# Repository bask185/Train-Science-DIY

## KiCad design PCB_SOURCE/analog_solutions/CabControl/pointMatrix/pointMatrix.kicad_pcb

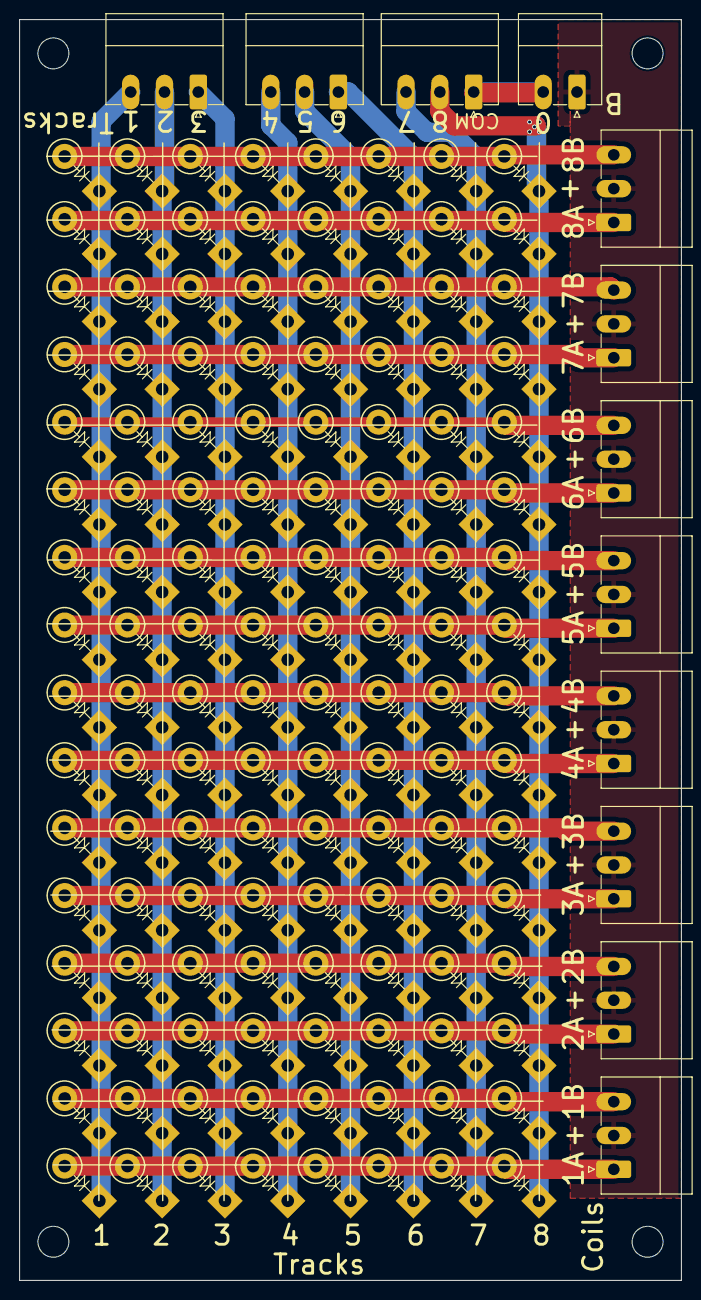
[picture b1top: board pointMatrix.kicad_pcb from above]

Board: 2 copper layers, 68.5 x 130.5 mm, 140 parts (0 on the bottom side), 26 nets.

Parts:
D1101, D1102, D1103, D1104, D1105, D1106, D1107, D1108, D1201, D1202, D1203, D1204, D1205, D1206, D1207, D1208, D1301, D1302, D1303, D1304, D1305, D1306, D1307, D1308, D1401, D1402, D1403, D1404, D1405, D1406, D1407, D1408, D1501, D1502, D1503, D1504, D1505, D1506, D1507, D1508, D1601, D1602, D1603, D1604, D1605, D1606, D1607, D1608, D1701, D1702, D1703, D1704, D1705, D1706, D1707, D1708, D1801, D1802, D1803, D1804, D1805, D1806, D1807, D1808, D1901, D1902, D1903, D1904, D1905, D1906, D1907, D1908, D2001, D2002, D2003, D2004, D2005, D2006, D2007, D2008, D2101, D2102, D2103, D2104, D2105, D2106, D2107, D2108, D2201, D2202, D2203, D2204, D2205, D2206, D2207, D2208, D2301, D2302, D2303, D2304, D2305, D2306, D2307, D2308, D2401, D2402, D2403, D2404, D2405, D2406, D2407, D2408, D2501, D2502, D2503, D2504, D2505, D2506, D2507, D2508, D2601, D2602, D2603, D2604, D2605, D2606, D2607, D2608: D; diode4matrix
J201, J301, J401, J501, J601, J701, J801, J901, J2801, J2802, J2803: Screw_Terminal_01x03; PhoenixContact_MC_1,5_3-G-3.5_1x03_P3.50mm_Horizontal
J2701: Screw_Terminal_01x02; PhoenixContact_MC_1,5_2-G-3.5_1x02_P3.50mm_Horizontal

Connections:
/Matrix/1.A: D1101.2 (A), D1102.2 (A), D1103.2 (A), D1104.2 (A), D1105.2 (A), D1106.2 (A), D1107.2 (A), D1108.2 (A), J201.1
/Matrix/1.B: D1201.2 (A), D1202.2 (A), D1203.2 (A), D1204.2 (A), D1205.2 (A), D1206.2 (A), D1207.2 (A), D1208.2 (A), J201.3
/Matrix/2.A: D1301.2 (A), D1302.2 (A), D1303.2 (A), D1304.2 (A), D1305.2 (A), D1306.2 (A), D1307.2 (A), D1308.2 (A), J301.1
/Matrix/2.B: D1401.2 (A), D1402.2 (A), D1403.2 (A), D1404.2 (A), D1405.2 (A), D1406.2 (A), D1407.2 (A), D1408.2 (A), J301.3
/Matrix/3.A: D1501.2 (A), D1502.2 (A), D1503.2 (A), D1504.2 (A), D1505.2 (A), D1506.2 (A), D1507.2 (A), D1508.2 (A), J401.1
/Matrix/3.B: D1601.2 (A), D1602.2 (A), D1603.2 (A), D1604.2 (A), D1605.2 (A), D1606.2 (A), D1607.2 (A), D1608.2 (A), J401.3
/Matrix/4.A: D1701.2 (A), D1702.2 (A), D1703.2 (A), D1704.2 (A), D1705.2 (A), D1706.2 (A), D1707.2 (A), D1708.2 (A), J501.1
/Matrix/4.B: D1801.2 (A), D1802.2 (A), D1803.2 (A), D1804.2 (A), D1805.2 (A), D1806.2 (A), D1807.2 (A), D1808.2 (A), J501.3
/Matrix/5.A: D1901.2 (A), D1902.2 (A), D1903.2 (A), D1904.2 (A), D1905.2 (A), D1906.2 (A), D1907.2 (A), D1908.2 (A), J601.1
/Matrix/5.B: D2001.2 (A), D2002.2 (A), D2003.2 (A), D2004.2 (A), D2005.2 (A), D2006.2 (A), D2007.2 (A), D2008.2 (A), J601.3
/Matrix/6.A: D2101.2 (A), D2102.2 (A), D2103.2 (A), D2104.2 (A), D2105.2 (A), D2106.2 (A), D2107.2 (A), D2108.2 (A), J701.1
/Matrix/6.B: D2201.2 (A), D2202.2 (A), D2203.2 (A), D2204.2 (A), D2205.2 (A), D2206.2 (A), D2207.2 (A), D2208.2 (A), J701.3
/Matrix/7.A: D2301.2 (A), D2302.2 (A), D2303.2 (A), D2304.2 (A), D2305.2 (A), D2306.2 (A), D2307.2 (A), D2308.2 (A), J801.1
/Matrix/7.B: D2401.2 (A), D2402.2 (A), D2403.2 (A), D2404.2 (A), D2405.2 (A), D2406.2 (A), D2407.2 (A), D2408.2 (A), J801.3
/Matrix/8.A: D2501.2 (A), D2502.2 (A), D2503.2 (A), D2504.2 (A), D2505.2 (A), D2506.2 (A), D2507.2 (A), D2508.2 (A), J901.1
/Matrix/8.B: D2601.2 (A), D2602.2 (A), D2603.2 (A), D2604.2 (A), D2605.2 (A), D2606.2 (A), D2607.2 (A), D2608.2 (A), J901.3
/Matrix/COL1: D1101.1 (K), D1201.1 (K), D1301.1 (K), D1401.1 (K), D1501.1 (K), D1601.1 (K), D1701.1 (K), D1801.1 (K), D1901.1 (K), D2001.1 (K), D2101.1 (K), D2201.1 (K), D2301.1 (K), D2401.1 (K), D2501.1 (K), D2601.1 (K), J2801.3
/Matrix/COL2: D1102.1 (K), D1202.1 (K), D1302.1 (K), D1402.1 (K), D1502.1 (K), D1602.1 (K), D1702.1 (K), D1802.1 (K), D1902.1 (K), D2002.1 (K), D2102.1 (K), D2202.1 (K), D2302.1 (K), D2402.1 (K), D2502.1 (K), D2602.1 (K), J2801.2
/Matrix/COL3: D1103.1 (K), D1203.1 (K), D1303.1 (K), D1403.1 (K), D1503.1 (K), D1603.1 (K), D1703.1 (K), D1803.1 (K), D1903.1 (K), D2003.1 (K), D2103.1 (K), D2203.1 (K), D2303.1 (K), D2403.1 (K), D2503.1 (K), D2603.1 (K), J2801.1
/Matrix/COL4: D1104.1 (K), D1204.1 (K), D1304.1 (K), D1404.1 (K), D1504.1 (K), D1604.1 (K), D1704.1 (K), D1804.1 (K), D1904.1 (K), D2004.1 (K), D2104.1 (K), D2204.1 (K), D2304.1 (K), D2404.1 (K), D2504.1 (K), D2604.1 (K), J2802.3
/Matrix/COL5: D1105.1 (K), D1205.1 (K), D1305.1 (K), D1405.1 (K), D1505.1 (K), D1605.1 (K), D1705.1 (K), D1805.1 (K), D1905.1 (K), D2005.1 (K), D2105.1 (K), D2205.1 (K), D2305.1 (K), D2405.1 (K), D2505.1 (K), D2605.1 (K), J2802.2
/Matrix/COL6: D1106.1 (K), D1206.1 (K), D1306.1 (K), D1406.1 (K), D1506.1 (K), D1606.1 (K), D1706.1 (K), D1806.1 (K), D1906.1 (K), D2006.1 (K), D2106.1 (K), D2206.1 (K), D2306.1 (K), D2406.1 (K), D2506.1 (K), D2606.1 (K), J2802.1
/Matrix/COL7: D1107.1 (K), D1207.1 (K), D1307.1 (K), D1407.1 (K), D1507.1 (K), D1607.1 (K), D1707.1 (K), D1807.1 (K), D1907.1 (K), D2007.1 (K), D2107.1 (K), D2207.1 (K), D2307.1 (K), D2407.1 (K), D2507.1 (K), D2607.1 (K), J2803.3
/Matrix/COL8: D1108.1 (K), D1208.1 (K), D1308.1 (K), D1408.1 (K), D1508.1 (K), D1608.1 (K), D1708.1 (K), D1808.1 (K), D1908.1 (K), D2008.1 (K), D2108.1 (K), D2208.1 (K), D2308.1 (K), D2408.1 (K), D2508.1 (K), D2608.1 (K), J2803.2
GND: J2701.2, J2803.1
VCC: J201.2, J301.2, J401.2, J501.2, J601.2, J701.2, J801.2, J901.2, J2701.1

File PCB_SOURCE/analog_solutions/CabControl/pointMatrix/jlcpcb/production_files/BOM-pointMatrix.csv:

Comment,Designator,Footprint,LCSC
D,D2504,diode4matrix,
D,D2207,diode4matrix,
D,D1904,diode4matrix,
D,D1907,diode4matrix,
D,D1701,diode4matrix,
D,D2402,diode4matrix,
D,D1702,diode4matrix,
D,D1404,diode4matrix,
D,D2005,diode4matrix,
D,D1308,diode4matrix,
D,D1707,diode4matrix,
D,D2103,diode4matrix,
D,D2003,diode4matrix,
D,D1303,diode4matrix,
D,D2008,diode4matrix,
D,D1706,diode4matrix,
D,D1806,diode4matrix,
D,D1304,diode4matrix,
D,D2301,diode4matrix,
D,D1807,diode4matrix,
Screw_Terminal_01x03,J801,"PhoenixContact_MC_1,5_3-G-3.5_1x03_P3.50mm_Horizontal",
D,D2303,diode4matrix,
D,D1101,diode4matrix,
D,D2604,diode4matrix,
D,D1902,diode4matrix,
D,D1305,diode4matrix,
D,D1207,diode4matrix,
D,D1608,diode4matrix,
D,D2403,diode4matrix,
D,D1705,diode4matrix,
D,D1105,diode4matrix,
D,D2204,diode4matrix,
D,D1802,diode4matrix,
D,D2601,diode4matrix,
D,D1301,diode4matrix,
D,D2608,diode4matrix,
D,D1808,diode4matrix,
D,D1601,diode4matrix,
D,D1903,diode4matrix,
D,D2307,diode4matrix,
D,D1401,diode4matrix,
D,D1803,diode4matrix,
D,D2507,diode4matrix,
D,D1603,diode4matrix,
Screw_Terminal_01x03,J501,"PhoenixContact_MC_1,5_3-G-3.5_1x03_P3.50mm_Horizontal",
D,D2503,diode4matrix,
Screw_Terminal_01x03,J901,"PhoenixContact_MC_1,5_3-G-3.5_1x03_P3.50mm_Horizontal",
D,D1202,diode4matrix,
D,D2406,diode4matrix,
D,D2102,diode4matrix,
D,D1104,diode4matrix,
D,D1103,diode4matrix,
D,D2104,diode4matrix,
D,D1203,diode4matrix,
D,D2107,diode4matrix,
D,D2101,diode4matrix,
D,D2205,diode4matrix,
Screw_Terminal_01x03,J201,"PhoenixContact_MC_1,5_3-G-3.5_1x03_P3.50mm_Horizontal",
D,D2602,diode4matrix,
D,D2202,diode4matrix,
D,D1501,diode4matrix,
D,D2405,diode4matrix,
D,D1908,diode4matrix,
D,D1108,diode4matrix,
D,D1605,diode4matrix,
D,D2501,diode4matrix,
D,D1102,diode4matrix,
D,D1504,diode4matrix,
D,D1901,diode4matrix,
D,D2603,diode4matrix,
D,D1307,diode4matrix,
D,D1703,diode4matrix,
D,D1406,diode4matrix,
D,D2606,diode4matrix,
D,D1205,diode4matrix,
D,D1602,diode4matrix,
D,D1604,diode4matrix,
D,D2305,diode4matrix,
Screw_Terminal_01x03,J401,"PhoenixContact_MC_1,5_3-G-3.5_1x03_P3.50mm_Horizontal",
D,D1408,diode4matrix,
D,D2401,diode4matrix,
D,D1204,diode4matrix,
D,D2306,diode4matrix,
D,D1704,diode4matrix,
D,D2106,diode4matrix,
D,D2001,diode4matrix,
D,D1405,diode4matrix,
D,D2304,diode4matrix,
D,D1508,diode4matrix,
Screw_Terminal_01x03,J601,"PhoenixContact_MC_1,5_3-G-3.5_1x03_P3.50mm_Horizontal",
D,D2408,diode4matrix,
D,D1607,diode4matrix,
D,D2201,diode4matrix,
D,D2208,diode4matrix,
D,D2506,diode4matrix,
D,D2302,diode4matrix,
D,D1905,diode4matrix,
D,D1505,diode4matrix,
Screw_Terminal_01x03,J2803,"PhoenixContact_MC_1,5_3-G-3.5_1x03_P3.50mm_Horizontal",
D,D1506,diode4matrix,
D,D2108,diode4matrix,
D,D1801,diode4matrix,
D,D1201,diode4matrix,
D,D2105,diode4matrix,
D,D2502,diode4matrix,
Screw_Terminal_01x03,J2802,"PhoenixContact_MC_1,5_3-G-3.5_1x03_P3.50mm_Horizontal",
D,D1906,diode4matrix,
D,D2404,diode4matrix,
D,D1107,diode4matrix,
D,D1804,diode4matrix,
D,D1407,diode4matrix,
D,D1402,diode4matrix,
D,D1208,diode4matrix,
Screw_Terminal_01x03,J701,"PhoenixContact_MC_1,5_3-G-3.5_1x03_P3.50mm_Horizontal",
D,D2505,diode4matrix,
D,D1306,diode4matrix,
D,D2006,diode4matrix,
Screw_Terminal_01x03,J301,"PhoenixContact_MC_1,5_3-G-3.5_1x03_P3.50mm_Horizontal",
D,D1502,diode4matrix,
D,D1403,diode4matrix,
D,D2508,diode4matrix,
D,D2206,diode4matrix,
D,D1503,diode4matrix,
D,D1106,diode4matrix,
D,D2407,diode4matrix,
D,D1708,diode4matrix,
D,D1507,diode4matrix,
D,D1805,diode4matrix,
D,D1302,diode4matrix,
D,D2605,diode4matrix,
D,D2308,diode4matrix,
Screw_Terminal_01x03,J2801,"PhoenixContact_MC_1,5_3-G-3.5_1x03_P3.50mm_Horizontal",
D,D2203,diode4matrix,
D,D1606,diode4matrix,
Screw_Terminal_01x02,J2701,"PhoenixContact_MC_1,5_2-G-3.5_1x02_P3.50mm_Horizontal",
D,D2007,diode4matrix,
D,D2004,diode4matrix,
D,D2607,diode4matrix,
D,D1206,diode4matrix,
D,D2002,diode4matrix,

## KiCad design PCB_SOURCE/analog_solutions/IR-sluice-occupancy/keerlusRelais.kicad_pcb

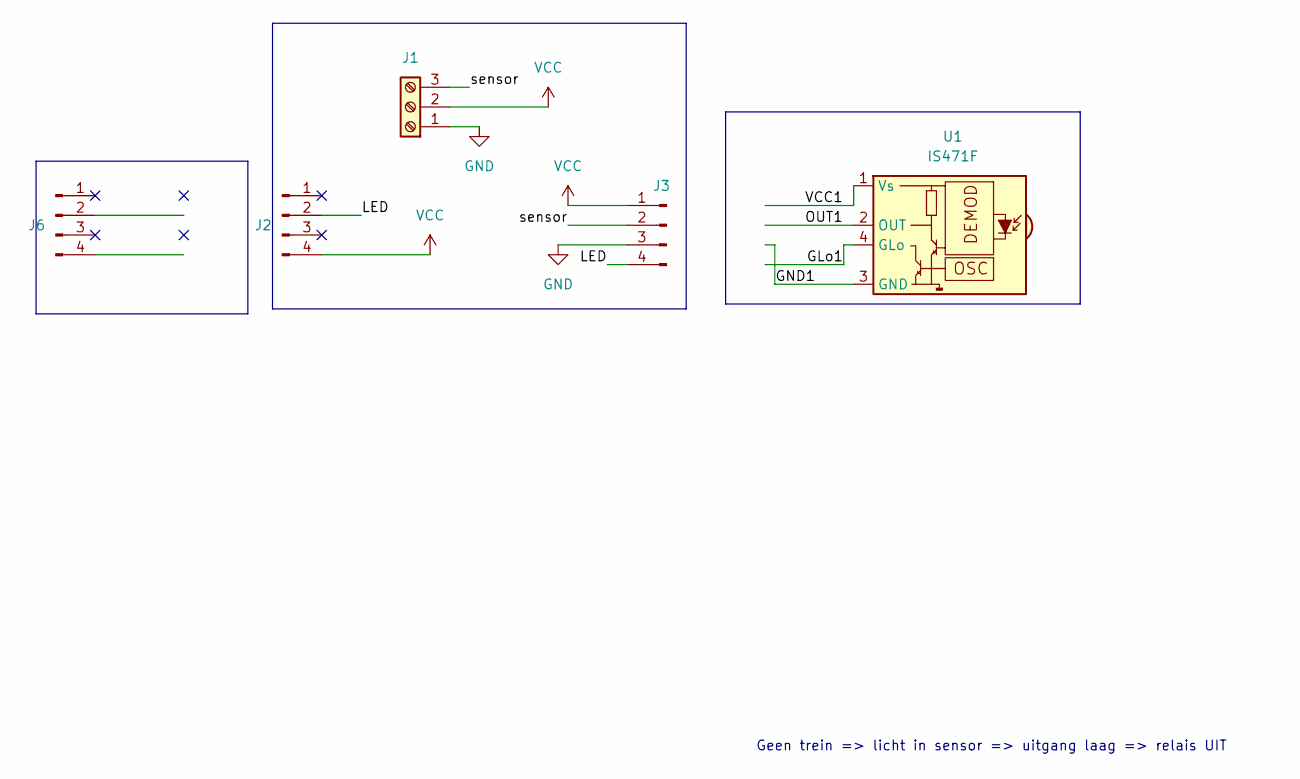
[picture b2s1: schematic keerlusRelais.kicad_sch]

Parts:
J1: Screw_Terminal_01x03; PhoenixContact_MCV_1,5_3-G-3.5_1x03_P3.50mm_Vertical
J2, J3: Conn_01x04_Pin; IR_EXTENDER_CUTOUT
J6: Conn_01x04_Pin; IR_EXTENDER_PCB
U1: IS471F; IR_EXTENDER_PCB

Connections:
/GLo1: U1.4 (GLo)
/GND1: U1.3 (GND)
/LED: J2.2, J3.4
/OUT1: U1.2 (OUT)
/VCC1: U1.1 (Vs)
/sensor: J1.3, J3.2
GND: J1.1, J3.3
VCC: J1.2, J2.4, J3.1

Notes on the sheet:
Geen trein => licht in sensor => uitgang laag => relais UIT

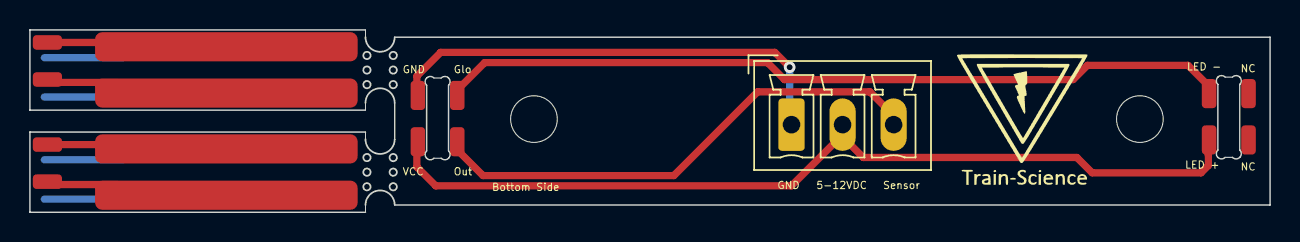
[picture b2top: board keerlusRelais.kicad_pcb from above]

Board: 2 copper layers, 85.0 x 12.5 mm, 5 parts (0 on the bottom side), 4 nets.

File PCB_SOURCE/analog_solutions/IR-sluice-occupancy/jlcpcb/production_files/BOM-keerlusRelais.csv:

Comment,Designator,Footprint,LCSC
IS471F,U1,IR_EXTENDER_PCB,
Screw_Terminal_01x03,J1,"PhoenixContact_MCV_1,5_3-G-3.5_1x03_P3.50mm_Vertical",
Conn_01x04_Pin,J6,IR_EXTENDER_PCB,
Conn_01x04_Pin,J2,IR_EXTENDER_CUTOUT,
Conn_01x04_Pin,J3,IR_EXTENDER_CUTOUT,

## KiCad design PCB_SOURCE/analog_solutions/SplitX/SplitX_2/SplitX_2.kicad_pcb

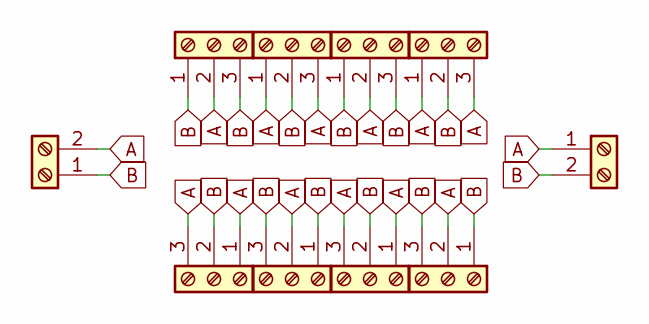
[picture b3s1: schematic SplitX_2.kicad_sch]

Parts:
J1, J10: Screw_Terminal_01x02; TerminalBlock_Phoenix_MKDS-1,5-2-5.08_1x02_P5.08mm_Horizont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; JLCPCB Part# C7471346
J2, J3, J4, J6, J7, J8, J9: Screw_Terminal_01x03; TerminalBlock_Phoenix_MKDS-1,5-3-5.08_1x03_P5.08mm_Horizont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; JLCPCB Part# C7471347
J5: Screw_Terminal_01x03; TerminalBlock_Phoenix_MKDS-1,5-3-5.08_1x03_P5.08mm_Horizont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

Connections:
A: J1.2, J2.2, J3.1, J3.3, J4.1, J4.3, J5.2, J6.2, J7.1, J7.3, J8.1, J8.3, J9.2, J10.1
B: J1.1, J2.1, J2.3, J3.2, J4.2, J5.1, J5.3, J6.1, J6.3, J7.2, J8.2, J9.1, J9.3, J10.2

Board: 2 copper layers, 10 parts (0 on the bottom side), 2 nets, no tracks yet.

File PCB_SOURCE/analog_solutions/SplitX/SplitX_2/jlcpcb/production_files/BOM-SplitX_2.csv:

Comment,Designator,Footprint,LCSC
Screw_Terminal_01x02,"J1,J10","TerminalBlock_Phoenix_MKDS-1,5-2-5.08_1x02_P5.08mm_Horizontal",C7471346
Screw_Terminal_01x03,"J2,J3,J4,J5,J6,J7,J8,J9","TerminalBlock_Phoenix_MKDS-1,5-3-5.08_1x03_P5.08mm_Horizontal",C7471347

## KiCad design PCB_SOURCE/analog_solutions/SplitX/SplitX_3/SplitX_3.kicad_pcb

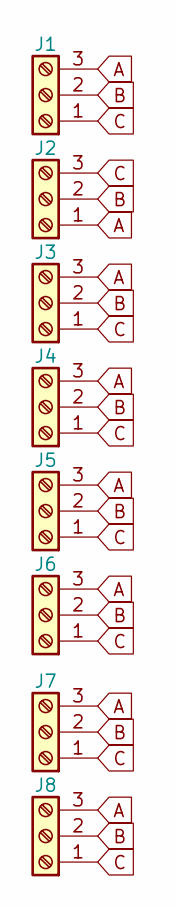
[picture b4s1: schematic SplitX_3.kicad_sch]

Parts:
J1, J2, J3, J4, J6, J7, J8: Screw_Terminal_01x03; TerminalBlock_Phoenix_MKDS-1,5-3-5.08_1x03_P5.08mm_Horizont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
J5: (no value)

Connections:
A: J1.3, J2.1, J3.3, J4.3, J5.3, J6.3, J7.3, J8.3
B: J1.2, J2.2, J3.2, J4.2, J5.2, J6.2, J7.2, J8.2
C: J1.1, J2.3, J3.1, J4.1, J5.1, J6.1, J7.1, J8.1

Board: 4 copper layers, 8 parts (0 on the bottom side), 3 nets, no tracks yet.

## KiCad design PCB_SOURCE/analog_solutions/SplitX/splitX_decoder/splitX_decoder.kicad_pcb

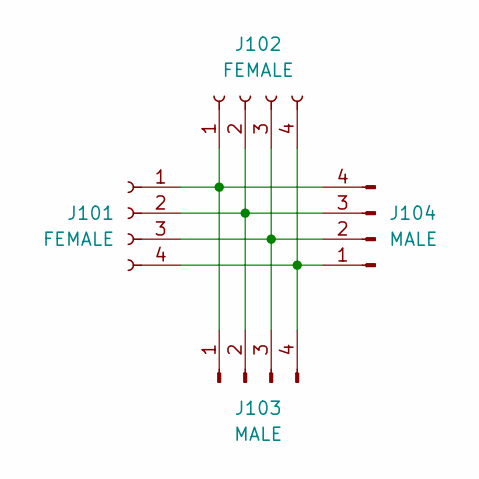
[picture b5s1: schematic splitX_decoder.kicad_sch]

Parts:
J101, J102: FEMALE; PhoenixContact_MC_1,5_4-G-3.5_1x04_P3.50mm_Horizontal
J103, J104: MALE; connector_3.50mm_4P horizontal_MALE

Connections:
unnamed: J101.1, J102.1, J103.1, J104.4
unnamed: J101.2, J102.2, J103.2, J104.3
unnamed: J101.3, J102.3, J103.3, J104.2
unnamed: J101.4, J102.4, J103.4, J104.1

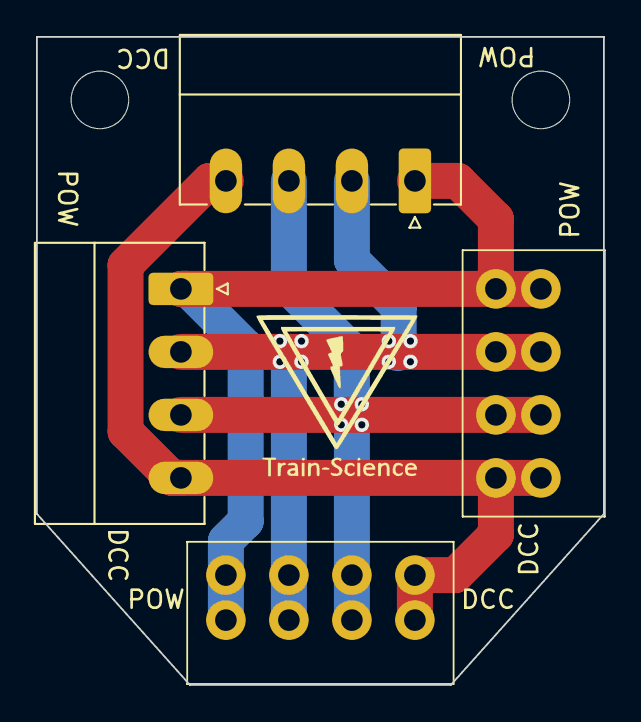
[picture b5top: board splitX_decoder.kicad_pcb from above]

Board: 2 copper layers, 31.5 x 36.0 mm, 4 parts (0 on the bottom side), 4 nets.

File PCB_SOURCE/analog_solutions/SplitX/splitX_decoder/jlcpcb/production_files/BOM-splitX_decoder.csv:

Comment,Designator,Footprint,LCSC
MALE,J104,connector_3.50mm_4P horizontal_MALE,
MALE,J103,connector_3.50mm_4P horizontal_MALE,
FEMALE,J102,"PhoenixContact_MC_1,5_4-G-3.5_1x04_P3.50mm_Horizontal",
FEMALE,J101,"PhoenixContact_MC_1,5_4-G-3.5_1x04_P3.50mm_Horizontal",

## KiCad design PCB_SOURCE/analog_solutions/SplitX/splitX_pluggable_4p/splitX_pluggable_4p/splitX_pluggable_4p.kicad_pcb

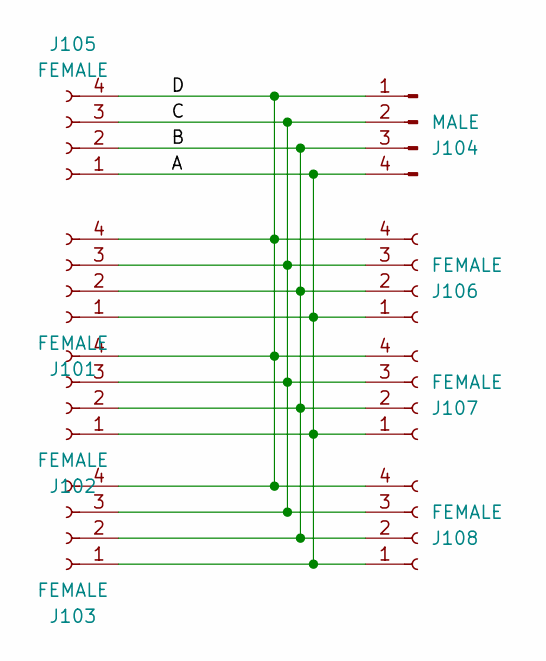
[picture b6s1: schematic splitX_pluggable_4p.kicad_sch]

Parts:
J101, J102, J103, J105, J106, J107, J108: FEMALE; PhoenixContact_MC_1,5_4-G-3.5_1x04_P3.50mm_Horizontal
J104: MALE; connector_3.50mm_4P horizontal_MALE

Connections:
/A: J101.1, J102.1, J103.1, J104.4, J105.1, J106.1, J107.1, J108.1
/B: J101.2, J102.2, J103.2, J104.3, J105.2, J106.2, J107.2, J108.2
/C: J101.3, J102.3, J103.3, J104.2, J105.3, J106.3, J107.3, J108.3
/D: J101.4, J102.4, J103.4, J104.1, J105.4, J106.4, J107.4, J108.4

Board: 4 copper layers, 8 parts (0 on the bottom side), 4 nets, no tracks yet.

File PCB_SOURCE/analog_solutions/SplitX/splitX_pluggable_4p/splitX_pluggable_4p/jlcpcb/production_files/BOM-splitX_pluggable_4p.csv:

Comment,Designator,Footprint,LCSC
FEMALE,J108,"PhoenixContact_MC_1,5_4-G-3.5_1x04_P3.50mm_Horizontal",
FEMALE,J107,"PhoenixContact_MC_1,5_4-G-3.5_1x04_P3.50mm_Horizontal",
FEMALE,J106,"PhoenixContact_MC_1,5_4-G-3.5_1x04_P3.50mm_Horizontal",
FEMALE,J105,"PhoenixContact_MC_1,5_4-G-3.5_1x04_P3.50mm_Horizontal",
MALE,J104,connector_3.50mm_4P horizontal_MALE,
FEMALE,J103,"PhoenixContact_MC_1,5_4-G-3.5_1x04_P3.50mm_Horizontal",
FEMALE,J102,"PhoenixContact_MC_1,5_4-G-3.5_1x04_P3.50mm_Horizontal",
FEMALE,J101,"PhoenixContact_MC_1,5_4-G-3.5_1x04_P3.50mm_Horizontal",
